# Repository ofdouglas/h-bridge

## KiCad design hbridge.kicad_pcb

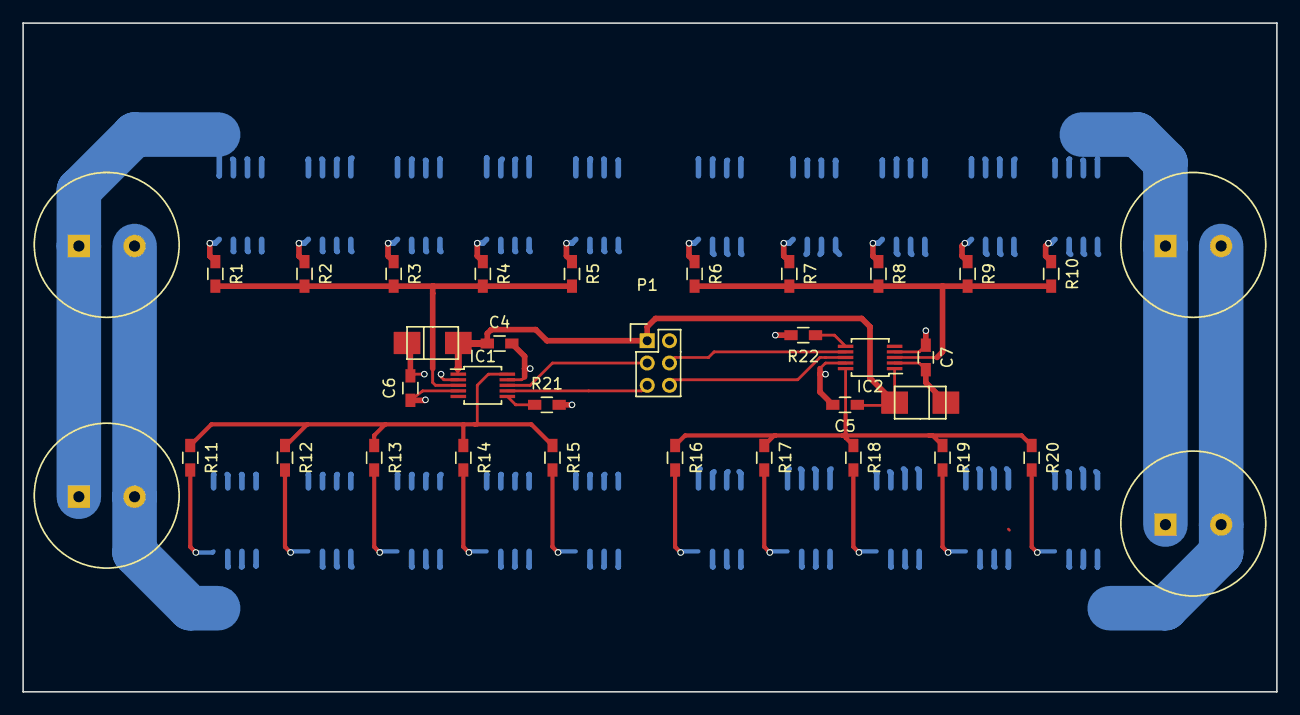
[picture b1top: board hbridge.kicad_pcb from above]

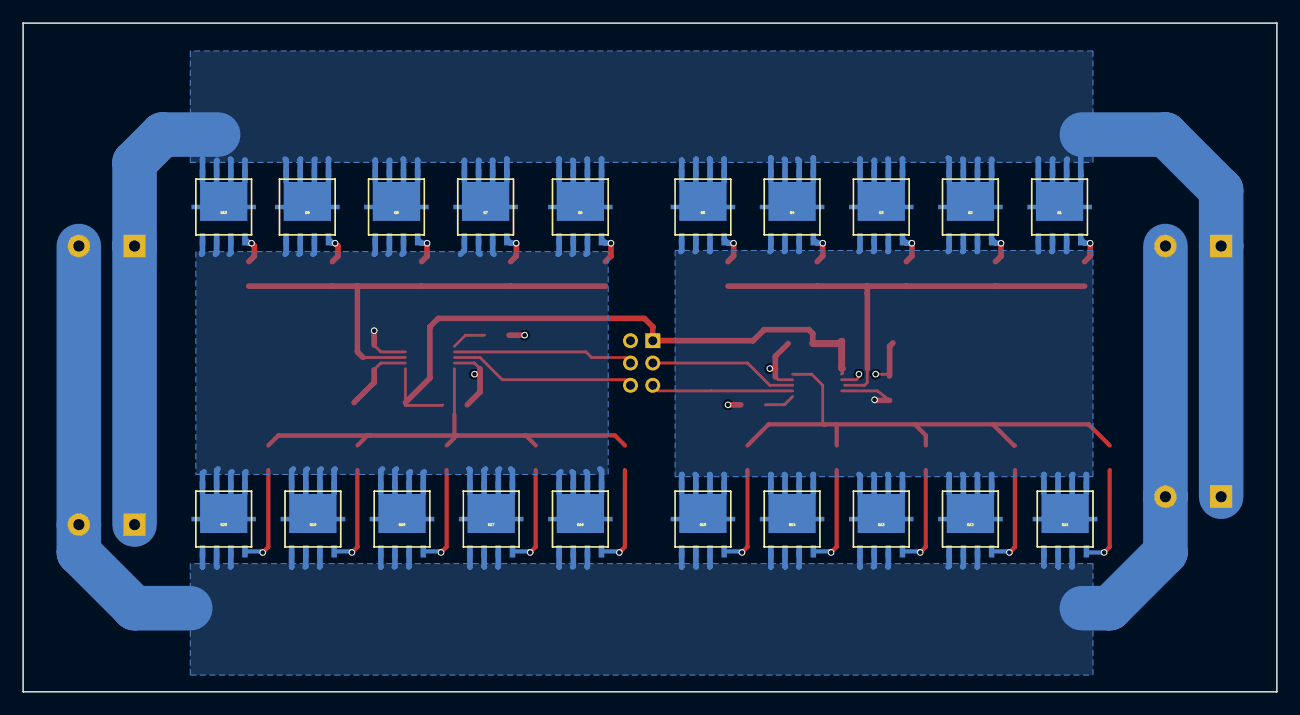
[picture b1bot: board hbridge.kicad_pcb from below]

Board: 4 copper layers, 112.5 x 60.0 mm, 55 parts (20 on the bottom side), 36 nets.

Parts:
C1, C2, C3, C8: 220u; CAP_RADIAL_13MM
C4, C5: 0.1u; R_0603_HandSoldering
C6, C7: 0.22u; R_0603_HandSoldering
D1, D2: MURA110T3G; DO-214AC-small
IC1, IC2: LM5106; MSOP-10_3x3mm_Pitch0.5mm
P1: CONN_02X03; Pin_Header_Straight_2x03_Pitch2.00mm
Q1, Q2, Q3, Q4, Q5, Q6, Q7, Q8, Q9, Q10, Q11, Q12, Q13, Q14, Q15, Q16, Q17, Q18, Q19, Q20: TPW4R50; DFN8-PWR
R1, R2, R3, R4, R5, R6, R7, R8, R9, R10, R11, R12, R13, R14, R15, R16, R17, R18, R19, R20: 10; R_0603_HandSoldering
R21, R22: 27k; R_0603_HandSoldering

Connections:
/DRV_1_IN: IC1.8, P1.3
/DRV_2_IN: IC2.8, P1.6
/DRV_EN: IC1.7, IC2.7, P1.4, P1.5
/HO1: IC1.3, R1.2, R2.2, R3.2, R4.2, R5.2
/HO2: IC2.3, R6.2, R7.2, R8.2, R9.2, R10.2
/LO1: IC1.10, R11.1, R12.1, R13.1, R14.1, R15.1
/LO2: IC2.10, R16.1, R17.1, R18.1, R19.1, R20.1
/M+: C6.1, IC1.4, Q1.3, Q2.3, Q3.3, Q4.3, Q5.3, Q11.2, Q12.2, Q13.2, Q14.2, Q15.2
/M-: C7.1, IC2.4, Q6.3, Q7.3, Q8.3, Q9.3, Q10.3, Q16.2, Q17.2, Q18.2, Q19.2, Q20.2
GND: C1.2, C2.2, C3.2, C4.2, C5.2, C8.2, IC1.9, IC2.9, P1.2, Q11.3, Q12.3, Q13.3, Q14.3, Q15.3, Q16.3, Q17.3, Q18.3, Q19.3, Q20.3, R21.2, R22.2
unnamed: C6.2, D1.1, IC1.2
unnamed: C7.2, D2.1, IC2.2
unnamed: IC1.6, R21.1
unnamed: IC2.6, R22.1
unnamed: Q1.1, R1.1
unnamed: Q2.1, R2.1
unnamed: Q3.1, R3.1
unnamed: Q4.1, R4.1
unnamed: Q5.1, R5.1
unnamed: Q6.1, R6.1
unnamed: Q7.1, R7.1
unnamed: Q8.1, R8.1
unnamed: Q9.1, R9.1
unnamed: Q10.1, R10.1
unnamed: Q11.1, R11.2
unnamed: Q12.1, R12.2
unnamed: Q13.1, R13.2
unnamed: Q14.1, R14.2
unnamed: Q15.1, R15.2
unnamed: Q16.1, R16.2
unnamed: Q17.1, R17.2
unnamed: Q18.1, R18.2
unnamed: Q19.1, R19.2
unnamed: Q20.1, R20.2
VCC: C1.1, C2.1, C3.1, C8.1, Q1.2, Q2.2, Q3.2, Q4.2, Q5.2, Q6.2, Q7.2, Q8.2, Q9.2, Q10.2
VDD: C4.1, C5.1, D1.2, D2.2, IC1.1, IC2.1, P1.1

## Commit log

2017-04-10 layout brainstorming
2017-04-11 First draft done
